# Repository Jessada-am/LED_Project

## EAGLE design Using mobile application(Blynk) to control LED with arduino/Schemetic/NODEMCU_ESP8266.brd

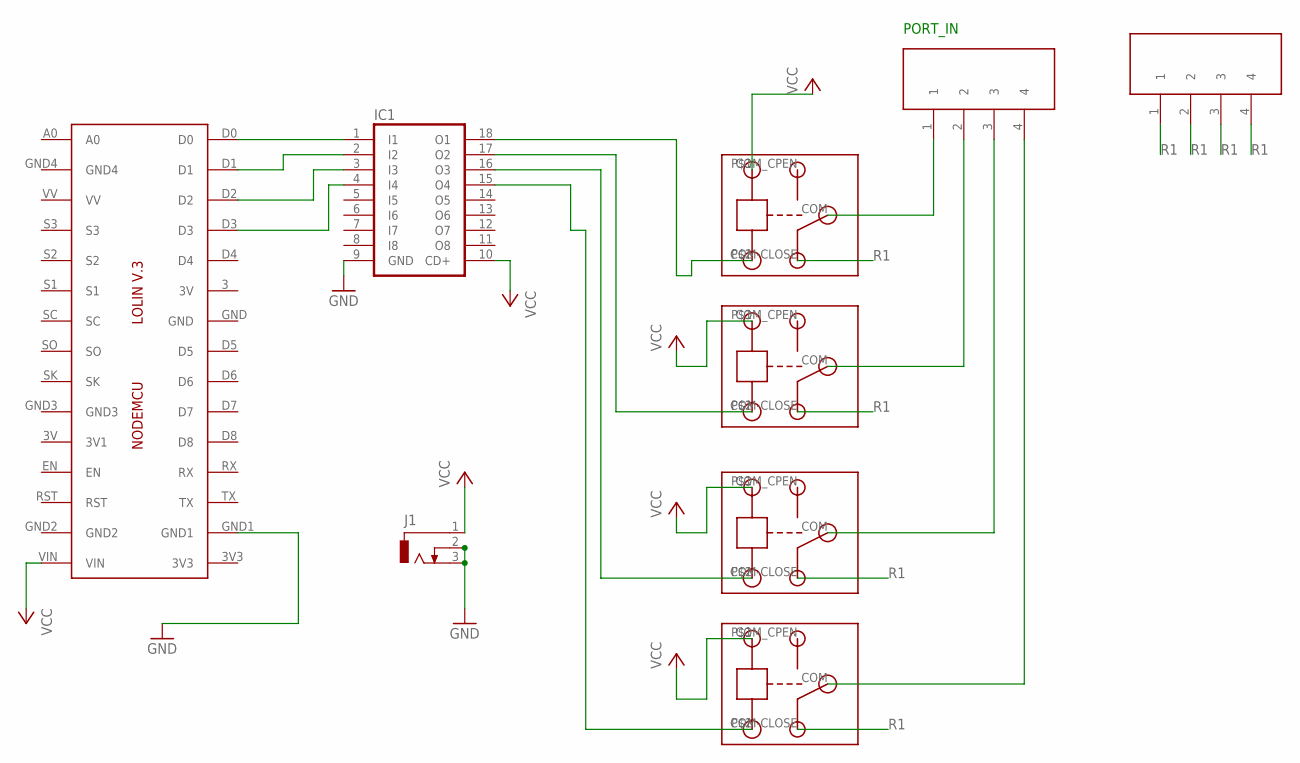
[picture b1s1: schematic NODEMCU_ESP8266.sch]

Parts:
IC1: ULN2803A; DIL18
IC2: LOLINV3
J1: DCJ0303
PORT_GND: LIB_TERMINAL_4_PORT_9.5MM
U$2, U$3, U$4, U$5: RELAY
U$6: LIB_TERMINAL_4_PORT_9.5MM

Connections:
GND: IC1.9 (GND), IC2.GND1, J1.2, J1.3
unnamed: IC1.1 (I1), IC2.D0
unnamed: IC1.2 (I2), IC2.D1
unnamed: IC1.3 (I3), IC2.D2
unnamed: IC1.4 (I4), IC2.D3
unnamed: IC1.18 (O1), U$5.P$2 (GND)
unnamed: IC1.17 (O2), U$3.P$2 (GND)
unnamed: IC1.16 (O3), U$2.P$2 (GND)
unnamed: IC1.15 (O4), U$4.P$2 (GND)
unnamed: U$5.COM, U$6.1
unnamed: U$3.COM, U$6.2
unnamed: U$2.COM, U$6.3
unnamed: U$4.COM, U$6.4
R1: PORT_GND.1, PORT_GND.2, PORT_GND.3, PORT_GND.4, U$2.COM-CLOSE, U$3.COM-CLOSE, U$4.COM-CLOSE, U$5.COM-CLOSE
VCC: IC1.10 (CD+), IC2.VIN, J1.1, U$2.P$1 (IN), U$3.P$1 (IN), U$4.P$1 (IN), U$5.P$1 (IN)

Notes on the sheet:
PORT_IN

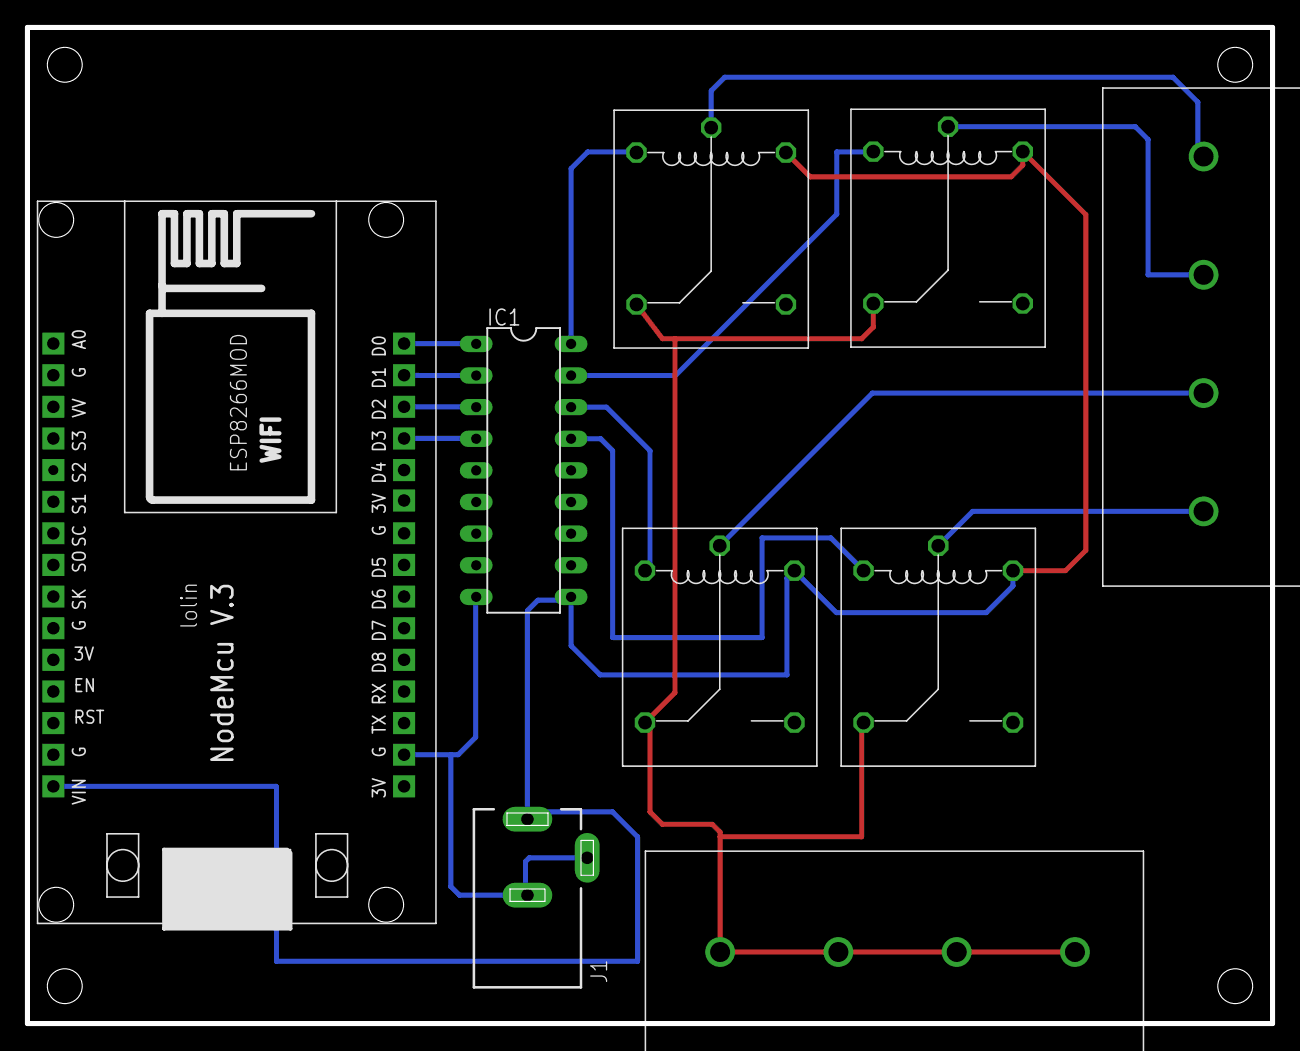
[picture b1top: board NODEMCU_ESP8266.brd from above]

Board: 2 copper layers, 100.0 x 80.0 mm, 9 parts (0 on the bottom side), 15 nets.

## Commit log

2019-05-24 Create LED_Dimmer_with_Cellphone
